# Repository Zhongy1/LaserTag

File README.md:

# LaserTag
Laser tag system: designs and code.

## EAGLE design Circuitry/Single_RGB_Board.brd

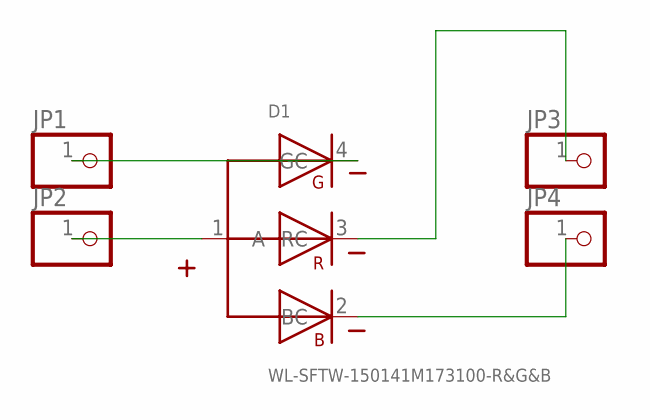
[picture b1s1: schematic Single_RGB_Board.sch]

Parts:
D1: WL-SFTW-150141M173100-R&G&B; 3528-COMMON-ANODE
JP1, JP2, JP3, JP4: PINHD-1X1; 1X01

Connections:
unnamed: D1.4 (GC), JP1.1
unnamed: D1.1 (A), JP2.1
unnamed: D1.3 (RC), JP3.1
unnamed: D1.2 (BC), JP4.1

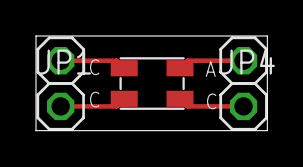
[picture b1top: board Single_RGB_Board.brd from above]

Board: 2 copper layers, 12.9 x 5.3 mm, 5 parts (0 on the bottom side), 4 nets.

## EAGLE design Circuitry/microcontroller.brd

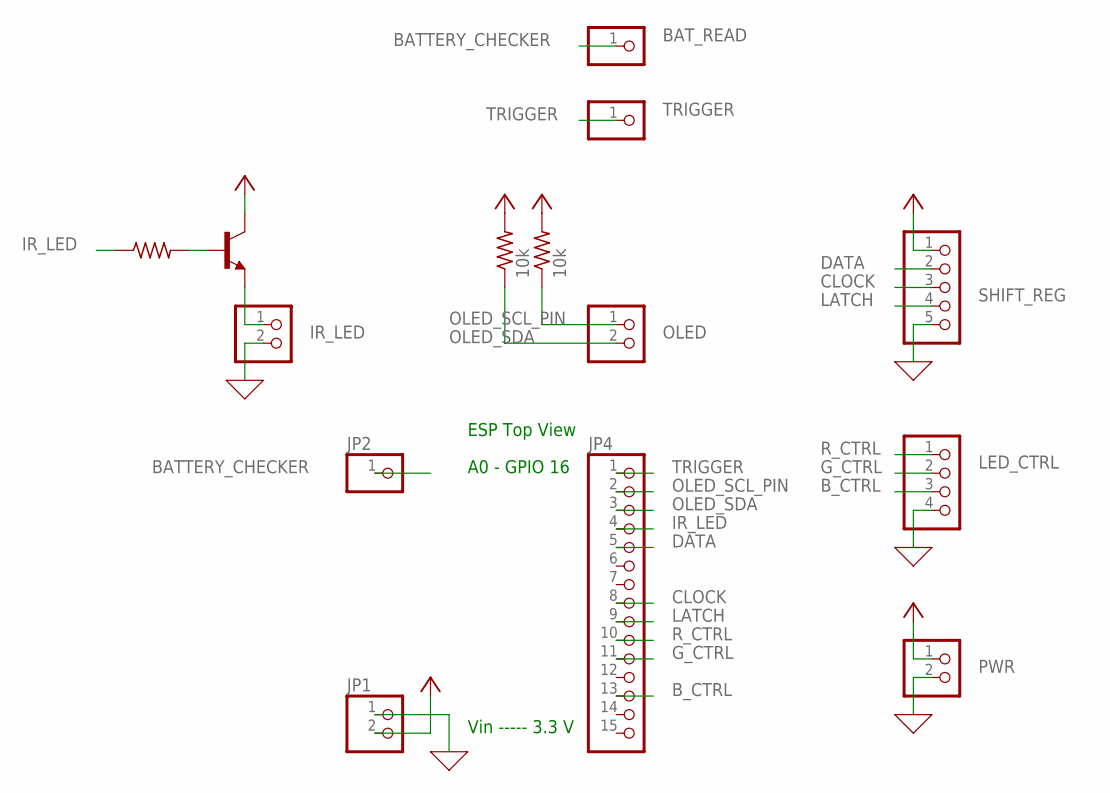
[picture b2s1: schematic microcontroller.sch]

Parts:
BAT_READ: PINHD-1X1; 1X01
IR_LED: PINHD-1X2; 1X02
IR_TRS: 2N5088; TO92
JP1: PINHD-1X2; 1X02
JP2: PINHD-1X1; 1X01
JP4: PINHD-1X15; 1X15
LED_CTRL: PINHD-1X4; 1X04
OLED: PINHD-1X2; 1X02
PWR: PINHD-1X2; 1X02
R1, R2: 10k; 0204/7
R3: R-US_0204/7; 0204/7
SHIFT_REG: PINHD-1X5; 1X05
TRIGGER: PINHD-1X1; 1X01

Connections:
0: IR_LED.2, JP1.1, LED_CTRL.4, PWR.2, SHIFT_REG.5
BATTERY_CHECKER: BAT_READ.1, JP2.1
B_CTRL: JP4.13, LED_CTRL.3
CLOCK: JP4.8, SHIFT_REG.3
DATA: JP4.5, SHIFT_REG.2
G_CTRL: JP4.11, LED_CTRL.2
IR_LED: JP4.4, R3.1
LATCH: JP4.9, SHIFT_REG.4
unnamed: IR_LED.1, IR_TRS.3 (E)
unnamed: IR_TRS.2 (B), R3.2
OLED_SCL_PIN: JP4.2, OLED.1, R1.1
OLED_SDA: JP4.3, OLED.2, R2.1
R_CTRL: JP4.10, LED_CTRL.1
TRIGGER: JP4.1, TRIGGER.1
VCC: IR_TRS.1 (C), JP1.2, PWR.1, R1.2, R2.2, SHIFT_REG.1

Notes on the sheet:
ESP Top View
A0 - GPIO 16
Vin ----- 3.3 V

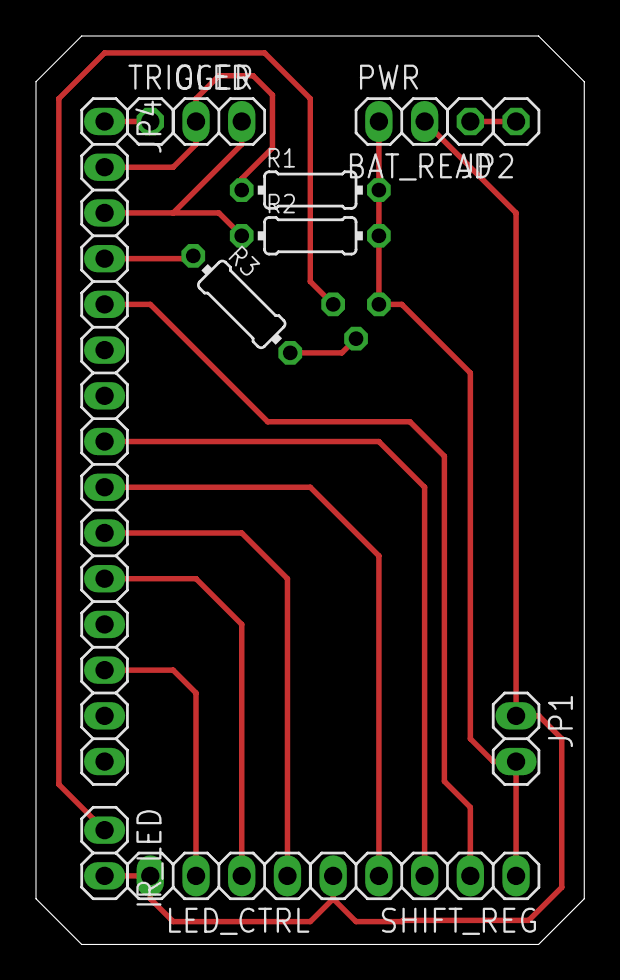
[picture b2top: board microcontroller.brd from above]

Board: 2 copper layers, 30.5 x 50.5 mm, 14 parts (1 on the bottom side), 15 nets.

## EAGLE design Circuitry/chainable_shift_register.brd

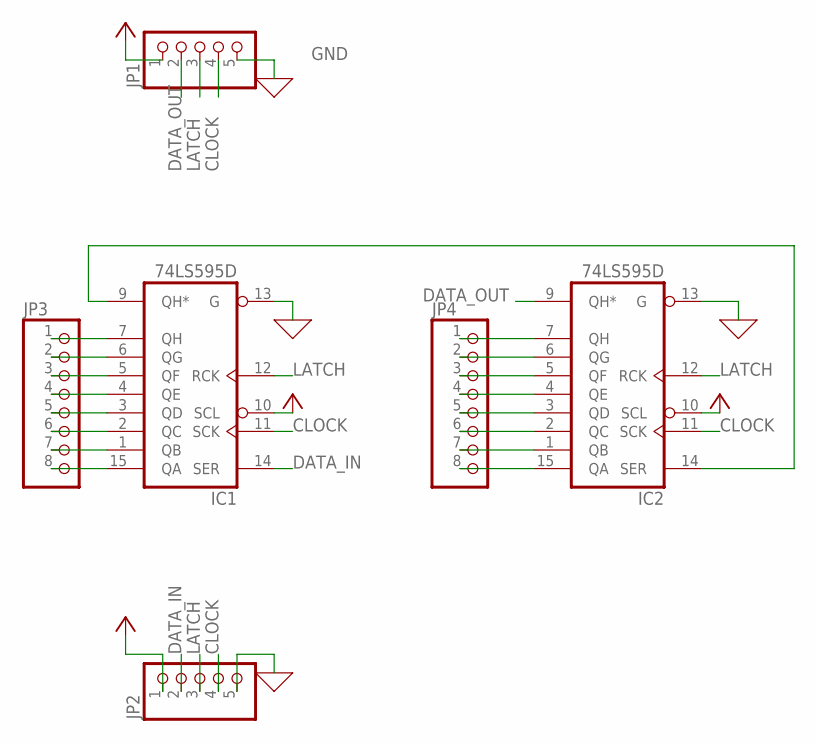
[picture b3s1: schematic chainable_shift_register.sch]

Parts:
IC1, IC2: 74LS595D; SO16
JP1, JP2: PINHD-1X5; 1X05
JP3, JP4: PINHD-1X8; 1X08

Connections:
CLOCK: IC1.11 (SCK), IC2.11 (SCK), JP1.4, JP2.4
DATA_IN: IC1.14 (SER), JP2.2
DATA_OUT: IC2.9 (QH*), JP1.2
GND: IC1.8 (GND), IC1.13 (G), IC2.8 (GND), IC2.13 (G), JP1.5, JP2.5
LATCH: IC1.12 (RCK), IC2.12 (RCK), JP1.3, JP2.3
unnamed: IC2.15 (QA), JP4.8
unnamed: IC2.1 (QB), JP4.7
unnamed: IC2.2 (QC), JP4.6
unnamed: IC2.3 (QD), JP4.5
unnamed: IC2.4 (QE), JP4.4
unnamed: IC2.5 (QF), JP4.3
unnamed: IC2.6 (QG), JP4.2
unnamed: IC2.7 (QH), JP4.1
unnamed: IC1.7 (QH), JP3.1
unnamed: IC1.6 (QG), JP3.2
unnamed: IC1.5 (QF), JP3.3
unnamed: IC1.4 (QE), JP3.4
unnamed: IC1.3 (QD), JP3.5
unnamed: IC1.2 (QC), JP3.6
unnamed: IC1.1 (QB), JP3.7
unnamed: IC1.15 (QA), JP3.8
unnamed: IC1.9 (QH*), IC2.14 (SER)
VCC: IC1.10 (SCL), IC1.16 (VCC), IC2.10 (SCL), IC2.16 (VCC), JP1.1, JP2.1

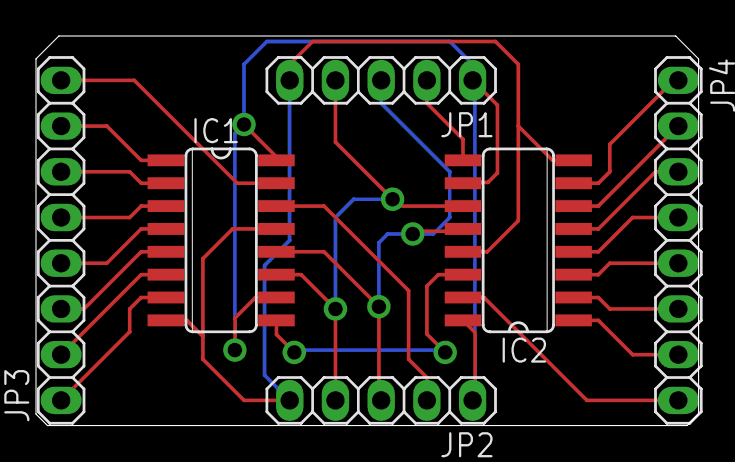
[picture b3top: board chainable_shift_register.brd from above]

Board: 2 copper layers, 36.8 x 21.6 mm, 6 parts (0 on the bottom side), 23 nets.

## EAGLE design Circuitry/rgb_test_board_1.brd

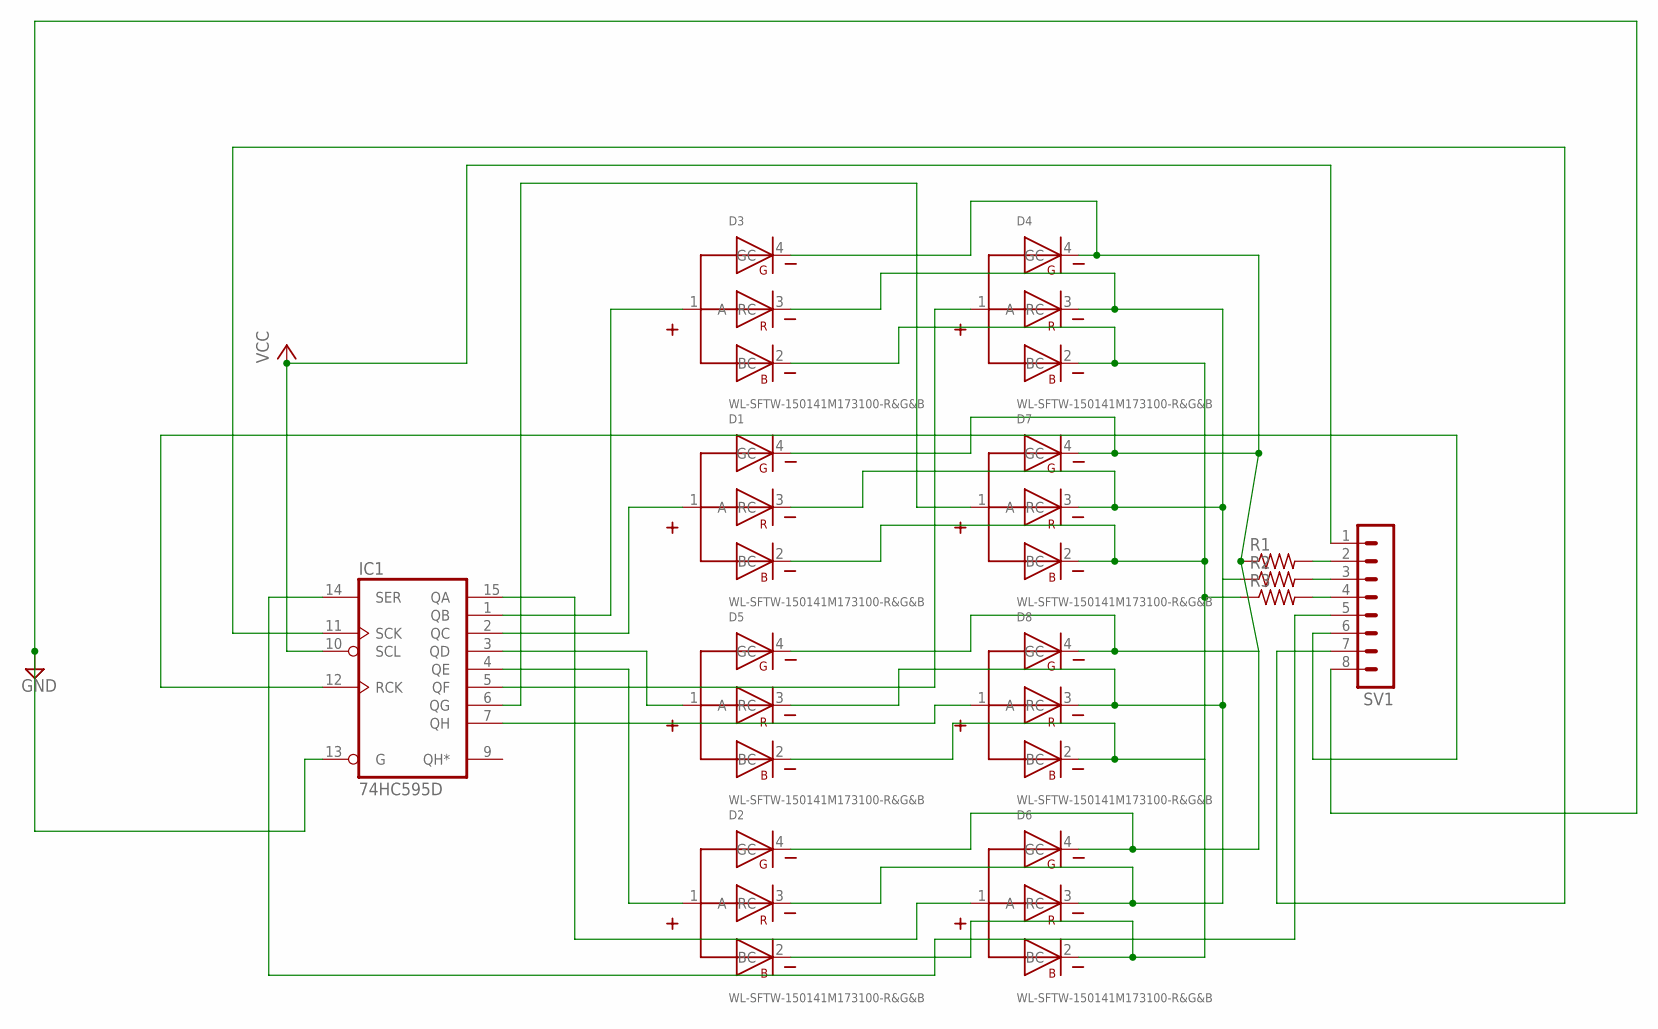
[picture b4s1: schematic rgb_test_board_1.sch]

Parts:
D1, D2, D3, D4, D5, D6, D7, D8: WL-SFTW-150141M173100-R&G&B; 3528-COMMON-ANODE
IC1: 74HC595D; SO16
R1, R2, R3: R-US_R0805; R0805
SV1: MA08-1

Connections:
GND: IC1.8 (GND), IC1.13 (G), SV1.8
unnamed: R1.2, SV1.2
unnamed: R2.2, SV1.3
unnamed: R3.2, SV1.4
unnamed: D3.1 (A), IC1.1 (QB)
unnamed: D1.1 (A), IC1.2 (QC)
unnamed: D5.1 (A), IC1.3 (QD)
unnamed: D2.1 (A), IC1.4 (QE)
unnamed: D4.1 (A), IC1.5 (QF)
unnamed: IC1.14 (SER), SV1.5
unnamed: D8.1 (A), IC1.7 (QH)
unnamed: D1.4 (GC), D2.4 (GC), D3.4 (GC), D4.4 (GC), D5.4 (GC), D6.4 (GC), D7.4 (GC), D8.4 (GC), R1.1
unnamed: IC1.12 (RCK), SV1.6
unnamed: D1.2 (BC), D2.2 (BC), D3.2 (BC), D4.2 (BC), D5.2 (BC), D6.2 (BC), D7.2 (BC), D8.2 (BC), R3.1
unnamed: D6.1 (A), IC1.15 (QA)
unnamed: D7.1 (A), IC1.6 (QG)
unnamed: D1.3 (RC), D2.3 (RC), D3.3 (RC), D4.3 (RC), D5.3 (RC), D6.3 (RC), D7.3 (RC), D8.3 (RC), R2.1
unnamed: IC1.11 (SCK), SV1.7
VCC: IC1.10 (SCL), IC1.16 (VCC), SV1.1

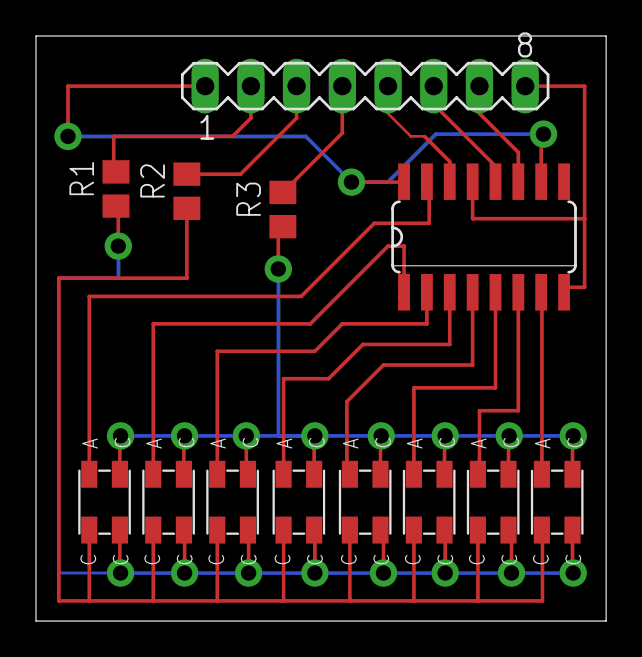
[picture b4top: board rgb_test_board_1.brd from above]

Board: 2 copper layers, 31.7 x 32.5 mm, 13 parts (0 on the bottom side), 19 nets.

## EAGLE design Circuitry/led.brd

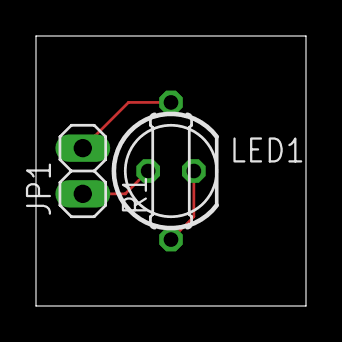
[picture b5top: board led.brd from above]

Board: 2 copper layers, 15.0 x 15.0 mm, 3 parts (0 on the bottom side), 3 nets.

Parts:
JP1: 1X02
LED1: LED5MM
R1: 0207/7

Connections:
unnamed: LED1.K, R1.1
unnamed: JP1.1, LED1.A
unnamed: JP1.2, R1.2

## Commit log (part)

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2019-09-19 Init subgroup folders/files
2019-09-19 add server folder
2019-09-27 made small change
2019-09-30 add websocket example
2019-10-07 init frame
2019-10-10 Create file and define basic class structure
2019-10-12 Make class exportable
2019-10-22 add connections between components
2019-10-23 Syntactical error fixed
2019-10-23 established ws connection
2019-10-25 string to String
2019-10-25 battery cutout
2019-10-30 add basic send with trigger interupt
2019-10-30 Add hex decoding functionality to server and refactor
2019-10-31 Add helper method for hex string validation
2019-11-01 add custom library
2019-11-05 place contacts onto board, no dimensions
2019-11-07 more changes to design
2019-11-08 add images
2019-11-15 need to measure LED
2019-11-15 add blaster_client code
2019-11-15 led cutout
2019-11-18 add batter contacts
2019-11-20 add counter for trigger pull
2019-11-21 move pieces around
2019-11-21 resolve merge conflicts
2019-12-06 add set output functionality
2019-12-31 improve microcontroller communication with server
2020-01-27 start attachment design
2020-01-28 Overhaul server structure with Nuxt.js
2020-01-29 Change front-end websocket connection signal
2020-02-03 save file changes
2020-02-03 actually save file for lenstachment
2020-02-04 Untrack nuxt build files
2020-02-05 create first rgb prototype
2020-02-10 create first test print for lenstatchment
2020-02-11 create second rgb prototype
2020-02-14 develop reload functionality
2020-02-17 adjust measurements
2020-02-19 add waiting room model
2020-02-19 Add player model
2020-02-24 file changes
2020-02-25 make requested changes
2020-02-25 init branch
2020-02-25 Added readme file
2020-02-26 Removed folder
2020-02-26 Mark some fields as readonly and reduce getters/setters
2020-02-26 Upload server class diagram
2020-03-03 create microcontroller board
2020-03-03 create chainable shift register board
2020-03-03 create single rgb board
2020-03-03 Create server controller
2020-03-04 lensTatchment
2020-03-05 redo measurements to fit
2020-03-10 created an rgb shift tester for 8 leds
2020-03-17 Rename lasertag_server.xml:Zone.Identifier to lasertag_server.xml.Zone.Identifier
2020-03-17 Rename blaster.ino to blaster_client.ino
2020-03-23 modify waitingroom constructor
2020-03-24 Disable strict mode
2020-03-24 Update class diagram with new methods and Command interface
2020-03-24 Remove parameters from waiting room constructor
2020-04-06 Update class properties and add team/scoring for players
2020-04-06 Create game room and define team logic
2020-04-07 Update class diagram and add flow diagram
2020-04-15 place components on temp prototype 2
2020-04-24 create a test piece for printing to test trigger mechanism
2020-04-24 create the new reciever_client program
2020-07-20 Bump lodash from 4.17.15 to 4.17.19 in /Server/Frontend
    Bumps [lodash](https://github.com/lodash/lodash) from 4.17.15 to 4.17.19.
    - [Release notes](https://github.com/lodash/lodash/releases)
    - [Commits](https://github.com/lodash/lodash/compare/4.17.15...4.17.19)
2020-08-01 Bump elliptic from 6.5.2 to 6.5.3 in /Server/Frontend
    Bumps [elliptic](https://github.com/indutny/elliptic) from 6.5.2 to 6.5.3.
    - [Release notes](https://github.com/indutny/elliptic/releases)
    - [Commits](https://github.com/indutny/elliptic/compare/v6.5.2...v6.5.3)
2020-11-25 Bump highlight.js from 9.18.1 to 9.18.5 in /Server/Frontend
    Bumps [highlight.js](https://github.com/highlightjs/highlight.js) from 9.18.1 to 9.18.5.
    - [Release notes](https://github.com/highlightjs/highlight.js/releases)
    - [Changelog](https://github.com/highlightjs/highlight.js/blob/9.18.5/CHANGES.md)
    - [Commits](https://github.com/highlightjs/highlight.js/compare/9.18.1...9.18.5)
2020-12-12 Bump ini from 1.3.5 to 1.3.8 in /Server/Backend
    Bumps [ini](https://github.com/isaacs/ini) from 1.3.5 to 1.3.8.
    - [Release notes](https://github.com/isaacs/ini/releases)
    - [Commits](https://github.com/isaacs/ini/compare/v1.3.5...v1.3.8)
2021-03-31 Bump y18n from 4.0.0 to 4.0.1 in /Server/Frontend
    Bumps [y18n](https://github.com/yargs/y18n) from 4.0.0 to 4.0.1.
    - [Release notes](https://github.com/yargs/y18n/releases)
    - [Changelog](https://github.com/yargs/y18n/blob/master/CHANGELOG.md)
    - [Commits](https://github.com/yargs/y18n/commits)
2021-04-30 Bump ssri from 6.0.1 to 6.0.2 in /Server/Frontend
    Bumps [ssri](https://github.com/npm/ssri) from 6.0.1 to 6.0.2.
    - [Release notes](https://github.com/npm/ssri/releases)
    - [Changelog](https://github.com/npm/ssri/blob/v6.0.2/CHANGELOG.md)
    - [Commits](https://github.com/npm/ssri/compare/v6.0.1...v6.0.2)
2021-05-11 Bump hosted-git-info from 2.8.8 to 2.8.9 in /Server/Frontend
    Bumps [hosted-git-info](https://github.com/npm/hosted-git-info) from 2.8.8 to 2.8.9.
    - [Release notes](https://github.com/npm/hosted-git-info/releases)
    - [Changelog](https://github.com/npm/hosted-git-info/blob/v2.8.9/CHANGELOG.md)
    - [Commits](https://github.com/npm/hosted-git-info/compare/v2.8.8...v2.8.9)
2021-05-28 Bump dns-packet from 1.3.1 to 1.3.4 in /Server/Frontend
    Bumps [dns-packet](https://github.com/mafintosh/dns-packet) from 1.3.1 to 1.3.4.
    - [Release notes](https://github.com/mafintosh/dns-packet/releases)
    - [Changelog](https://github.com/mafintosh/dns-packet/blob/master/CHANGELOG.md)
    - [Commits](https://github.com/mafintosh/dns-packet/compare/v1.3.1...v1.3.4)
2021-05-30 Bump ws from 7.2.3 to 7.4.6 in /Server/Backend
    Bumps [ws](https://github.com/websockets/ws) from 7.2.3 to 7.4.6.
    - [Release notes](https://github.com/websockets/ws/releases)
    - [Commits](https://github.com/websockets/ws/compare/7.2.3...7.4.6)
2021-06-06 Bump ws from 6.2.1 to 6.2.2 in /Server/Frontend
    Bumps [ws](https://github.com/websockets/ws) from 6.2.1 to 6.2.2.
    - [Release notes](https://github.com/websockets/ws/releases)
    - [Commits](https://github.com/websockets/ws/commits)
    ---
    updated-dependencies:
    - dependency-name: ws
2021-06-11 Bump normalize-url from 4.5.0 to 4.5.1 in /Server/Backend
    Bumps [normalize-url](https://github.com/sindresorhus/normalize-url) from 4.5.0 to 4.5.1.
    - [Release notes](https://github.com/sindresorhus/normalize-url/releases)
    - [Commits](https://github.com/sindresorhus/normalize-url/commits)
    ---
    updated-dependencies:
    - dependency-name: normalize-url
2021-06-17 Bump postcss from 7.0.27 to 7.0.36 in /Server/Frontend
    Bumps [postcss](https://github.com/postcss/postcss) from 7.0.27 to 7.0.36.
    - [Release notes](https://github.com/postcss/postcss/releases)
    - [Changelog](https://github.com/postcss/postcss/blob/main/CHANGELOG.md)
    - [Commits](https://github.com/postcss/postcss/compare/7.0.27...7.0.36)
    ---
    updated-dependencies:
2021-08-12 Bump path-parse from 1.0.6 to 1.0.7 in /Server/Frontend
    Bumps [path-parse](https://github.com/jbgutierrez/path-parse) from 1.0.6 to 1.0.7.
    - [Release notes](https://github.com/jbgutierrez/path-parse/releases)
    - [Commits](https://github.com/jbgutierrez/path-parse/commits/v1.0.7)
    ---
    updated-dependencies:
    - dependency-name: path-parse
2022-01-14 Bump follow-redirects from 1.14.0 to 1.14.7 in /Server/Frontend
    Bumps [follow-redirects](https://github.com/follow-redirects/follow-redirects) from 1.14.0 to 1.14.7.
    - [Release notes](https://github.com/follow-redirects/follow-redirects/releases)
    - [Commits](https://github.com/follow-redirects/follow-redirects/compare/v1.14.0...v1.14.7)
    ---
    updated-dependencies:
    - dependency-name: follow-redirects
2022-02-13 Bump ajv from 6.12.2 to 6.12.6 in /Server/Frontend
    Bumps [ajv](https://github.com/ajv-validator/ajv) from 6.12.2 to 6.12.6.
    - [Release notes](https://github.com/ajv-validator/ajv/releases)
    - [Commits](https://github.com/ajv-validator/ajv/compare/v6.12.2...v6.12.6)
    ---
    updated-dependencies:
    - dependency-name: ajv
2022-02-19 Bump url-parse from 1.5.1 to 1.5.7 in /Server/Frontend
    Bumps [url-parse](https://github.com/unshiftio/url-parse) from 1.5.1 to 1.5.7.
    - [Release notes](https://github.com/unshiftio/url-parse/releases)
    - [Commits](https://github.com/unshiftio/url-parse/compare/1.5.1...1.5.7)
    ---
    updated-dependencies:
    - dependency-name: url-parse
2022-03-26 Bump minimist from 1.2.5 to 1.2.6 in /Server/Backend
    Bumps [minimist](https://github.com/substack/minimist) from 1.2.5 to 1.2.6.
    - [Release notes](https://github.com/substack/minimist/releases)
    - [Commits](https://github.com/substack/minimist/compare/1.2.5...1.2.6)
    ---
    updated-dependencies:
    - dependency-name: minimist
2022-03-26 Bump minimist from 1.2.5 to 1.2.6 in /Server/Frontend
    Bumps [minimist](https://github.com/substack/minimist) from 1.2.5 to 1.2.6.
    - [Release notes](https://github.com/substack/minimist/releases)
    - [Commits](https://github.com/substack/minimist/compare/1.2.5...1.2.6)
    ---
    updated-dependencies:
    - dependency-name: minimist
2022-06-01 Bump eventsource from 1.1.0 to 1.1.1 in /Server/Frontend
    Bumps [eventsource](https://github.com/EventSource/eventsource) from 1.1.0 to 1.1.1.
    - [Release notes](https://github.com/EventSource/eventsource/releases)
    - [Changelog](https://github.com/EventSource/eventsource/blob/master/HISTORY.md)
    - [Commits](https://github.com/EventSource/eventsource/compare/v1.1.0...v1.1.1)
    ---
    updated-dependencies:
2022-06-23 Bump shell-quote from 1.7.2 to 1.7.3 in /Server/Frontend
    Bumps [shell-quote](https://github.com/substack/node-shell-quote) from 1.7.2 to 1.7.3.
    - [Release notes](https://github.com/substack/node-shell-quote/releases)
    - [Changelog](https://github.com/substack/node-shell-quote/blob/master/CHANGELOG.md)
    - [Commits](https://github.com/substack/node-shell-quote/compare/v1.7.2...1.7.3)
    ---
    updated-dependencies:
2022-07-21 Bump terser from 4.6.11 to 4.8.1 in /Server/Frontend
    Bumps [terser](https://github.com/terser/terser) from 4.6.11 to 4.8.1.
    - [Release notes](https://github.com/terser/terser/releases)
    - [Changelog](https://github.com/terser/terser/blob/master/CHANGELOG.md)
    - [Commits](https://github.com/terser/terser/commits)
    ---
    updated-dependencies:
2022-12-05 Bump decode-uri-component from 0.2.0 to 0.2.2 in /Server/Frontend
    Bumps [decode-uri-component](https://github.com/SamVerschueren/decode-uri-component) from 0.2.0 to 0.2.2.
    - [Release notes](https://github.com/SamVerschueren/decode-uri-component/releases)
    - [Commits](https://github.com/SamVerschueren/decode-uri-component/compare/v0.2.0...v0.2.2)
    ---
    updated-dependencies:
    - dependency-name: decode-uri-component
2022-12-11 Bump qs from 6.5.2 to 6.5.3 in /Server/Frontend
    Bumps [qs](https://github.com/ljharb/qs) from 6.5.2 to 6.5.3.
    - [Release notes](https://github.com/ljharb/qs/releases)
    - [Changelog](https://github.com/ljharb/qs/blob/main/CHANGELOG.md)
    - [Commits](https://github.com/ljharb/qs/compare/v6.5.2...v6.5.3)
    ---
    updated-dependencies:
2022-12-12 Bump express from 4.17.1 to 4.18.2 in /Server/Frontend
    Bumps [express](https://github.com/expressjs/express) from 4.17.1 to 4.18.2.
    - [Release notes](https://github.com/expressjs/express/releases)
    - [Changelog](https://github.com/expressjs/express/blob/master/History.md)
    - [Commits](https://github.com/expressjs/express/compare/4.17.1...4.18.2)
    ---
    updated-dependencies:

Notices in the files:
parts and their libraries:
Wurth_Elektronik_Optoelectronics_rev15b: Copyright: Würth Elektronik
